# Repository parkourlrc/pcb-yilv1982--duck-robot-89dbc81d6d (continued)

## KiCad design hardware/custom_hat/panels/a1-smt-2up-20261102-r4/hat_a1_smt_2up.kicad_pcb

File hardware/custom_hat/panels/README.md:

# HAT 制造拼板工作区

2026-11-03当前86654c03，[r18](a1-smt-2up-20261102-r18/README.md)。新增BMI088 0.5mm/0.2mm F.Cu电源支路；邮票孔居中、X108/160分板带局部退铜；修复第二单元Power映射。原生主板/拼板全0，两个0.175mm探针均被Power0.2规则拒绝。旧r1～r17退出制造入口；实际工艺/制造/完整机械与首板未验。见[证据](../../../docs/references/扩展板邮票孔与电源修复/research.md)。

**旧r1～r17及其制造副本均不作当前制造依据**。第二单元Power映射不足，原DRC0不能说明规则等价；旧r14完整PCBA ZIP保留历史，不覆写。旧单板资料按源SHA审查，无B2错误。

所有文件均是制造准备/候选，不授权下单或上电。源板未解决的问题不会因为复制进拼板而消失。

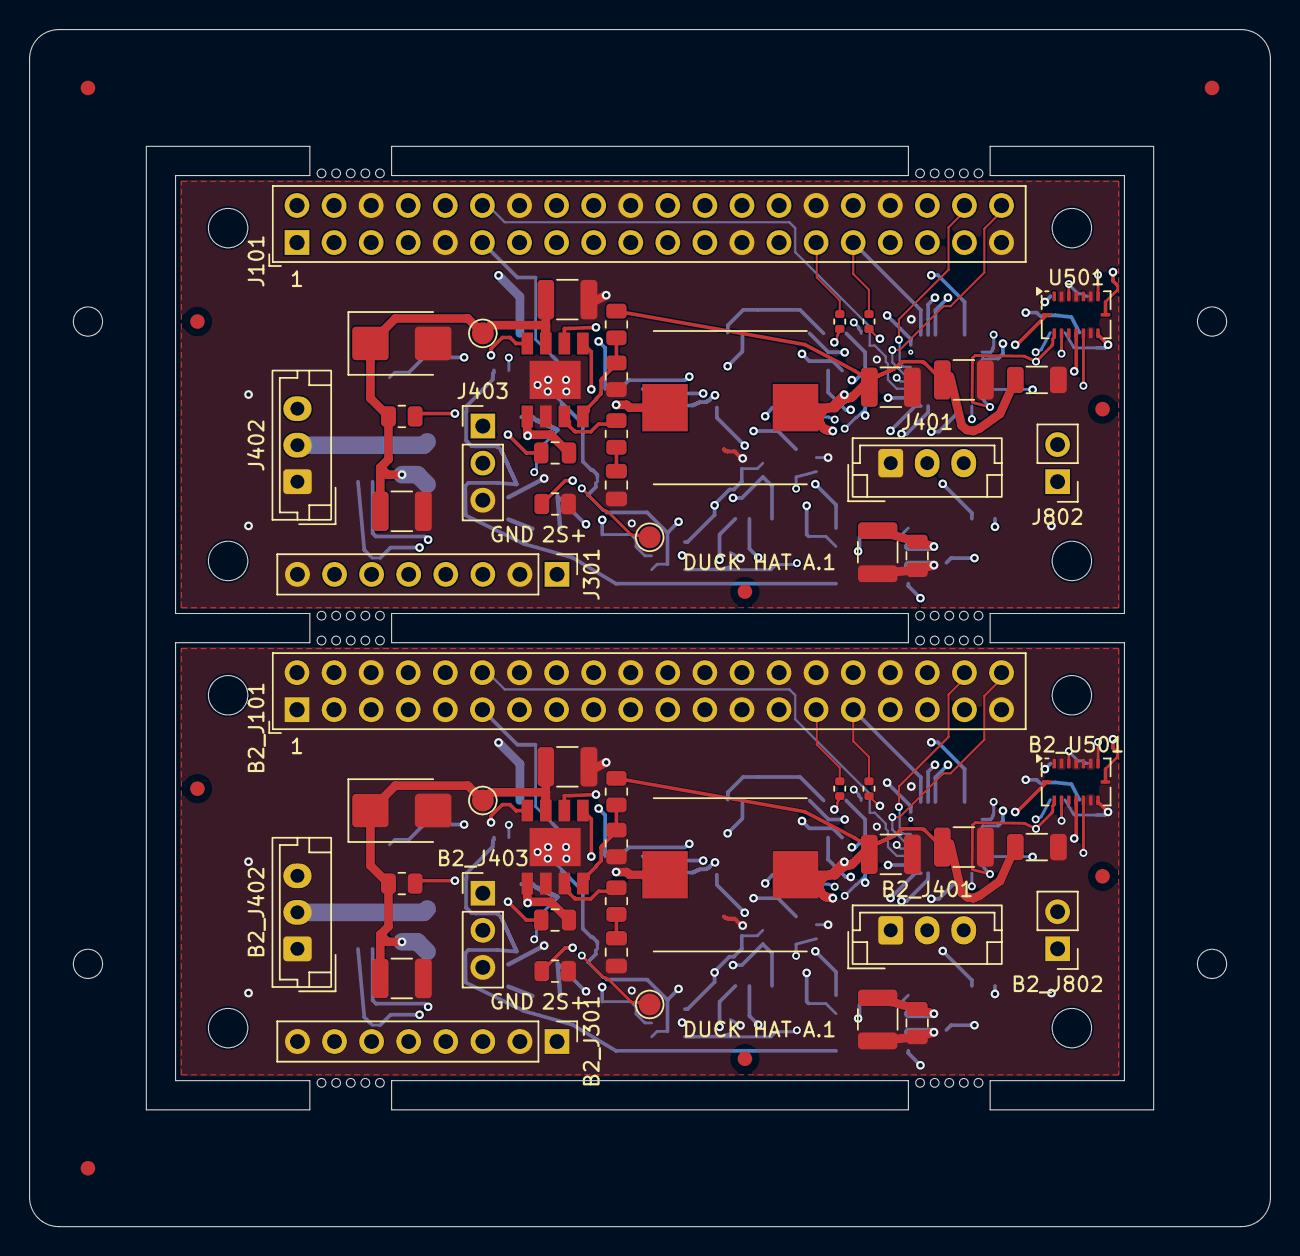
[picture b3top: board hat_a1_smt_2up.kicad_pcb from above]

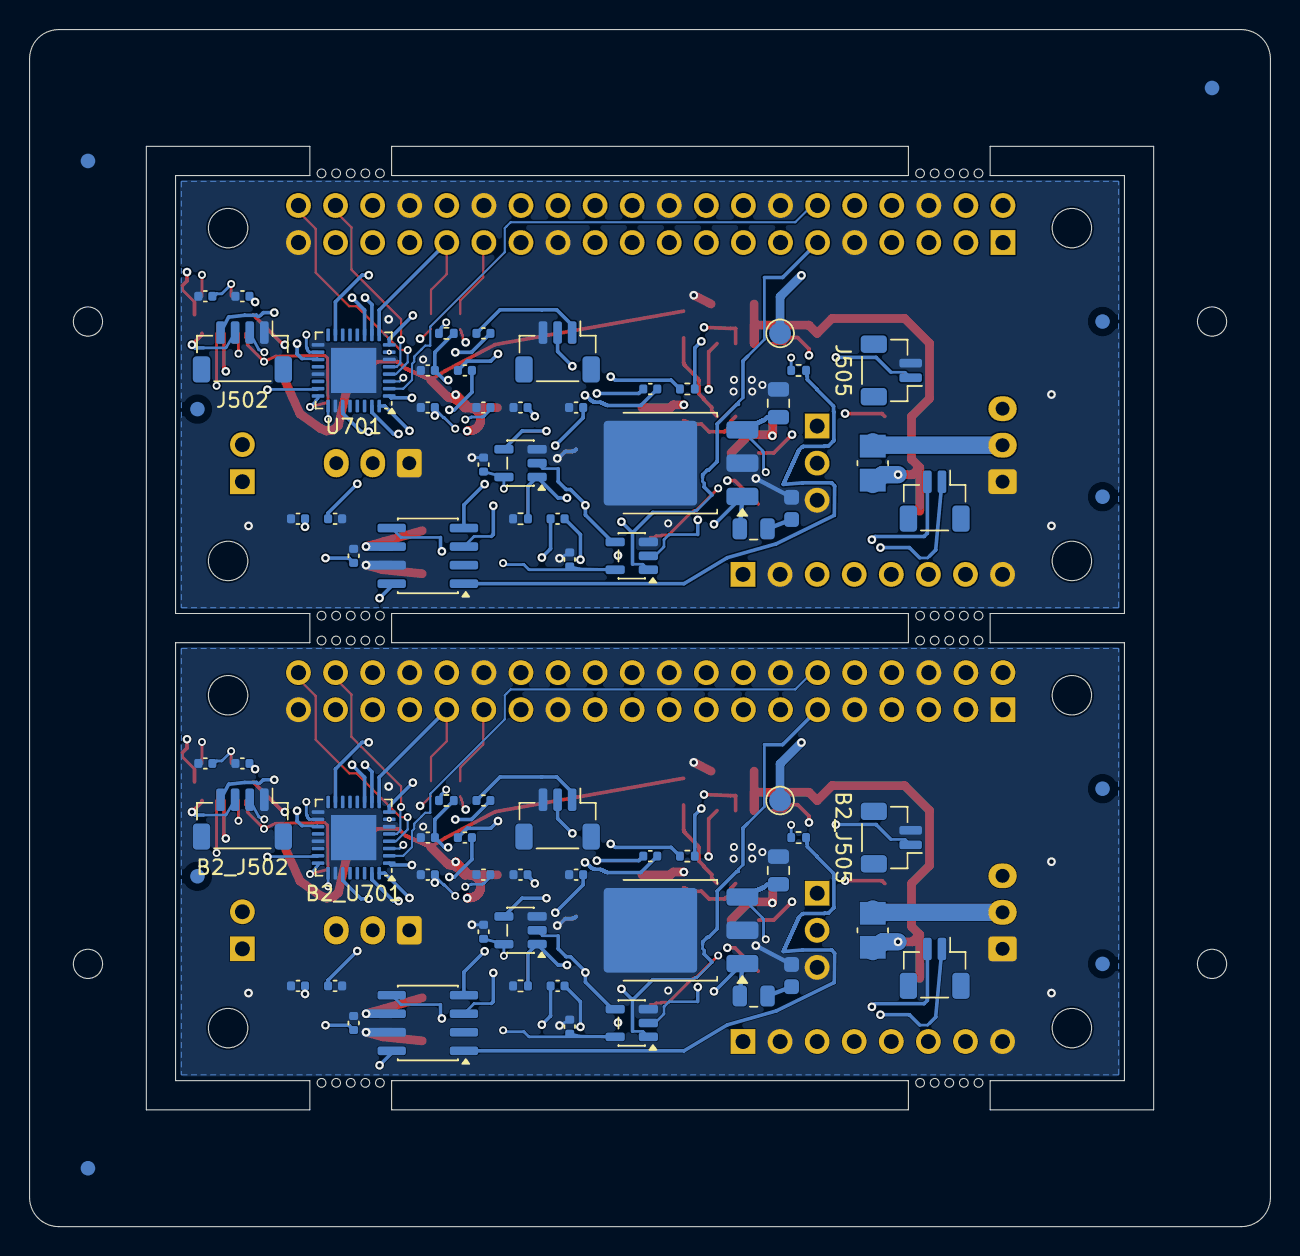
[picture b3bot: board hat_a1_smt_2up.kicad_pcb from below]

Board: 4 copper layers, 85.0 x 82.0 mm, 194 parts (77 on the bottom side), 84 nets.

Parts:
B2_C301: 3.3nF; C_0805_2012Metric
B2_C302: 100nF; C_0805_2012Metric
B2_C303, B2_C304, B2_C305, B2_C306, B2_C323: 22uF; C_1210_3225Metric
B2_C307: 22uF reserve; C_1206_3216Metric
B2_C308, B2_C328: 2.2uF; C_0805_2012Metric
B2_C309: 2.2uF; C_0805_2012Metric_LDO_ClearSilk
B2_C310, B2_C312, B2_C319, B2_C320, B2_C327, B2_C329, B2_C330: 100nF; C_0402_1005Metric
B2_C311, B2_C313, B2_C315, B2_C321, B2_C322, B2_C325, B2_C326: 1uF; C_0402_1005Metric
B2_C317, B2_C318: 10uF; C_0402_1005Metric
B2_D301: SMBJ12A (fitted); D_SMB
B2_FID1, B2_FID2, B2_FID3, B2_FID4, B2_FID5, B2_FID6: Fiducial_1mm_Mask2mm
B2_H1, B2_H2: MountingHole_2.7mm_M2.5; MountingHole_2.7_M2.5_Head4.5
B2_H3, B2_H4: MountingHole_2.7mm_M2.5
B2_J101: RADXA_ZERO_3W_40P; Radxa40P_Samtec_SSW120
B2_J301: POWER_AND_RAILS; Samtec_TSW108_07
B2_J401: DYNAMIXEL_TTL_1; JST_EH_B3B-EH-A_1x03_P2.50mm_Vertical
B2_J402: DYNAMIXEL_TTL_2; JST_EH_B3B-EH-A_1x03_P2.50mm_Vertical
B2_J403: HOST_UART2; Samtec_TSW103_07
B2_J502: TOF_I2C5; JST_SH_BM04B-SRSS-TB_1x04-1MP_P1.00mm_Vertical
B2_J504: AUDIO_OUT_SH; JST_SH_BM03B-SRSS-TB_1x03-1MP_P1.00mm_Vertical
B2_J505: MIC_IN; JST_SH_BM02B-SRSS-TB_1x02-1MP_P1.00mm_Vertical
B2_J506: SPEAKER; JST_SH_BM02B-SRSS-TB_1x02-1MP_P1.00mm_Vertical
B2_J802: IMU_INT_TP; Samtec_TSW102_07
B2_L301: 5.6uH; IHLP4040DZ_5A_Above2u2
B2_R301: 52.3k; R_0805_2012Metric
B2_R302: 10k; R_0805_2012Metric
B2_R303: 200k; R_0805_2012Metric
B2_R304: 14k; R_0805_2012Metric
B2_R305: 100k; R_0805_2012Metric
B2_R308: 10k; R_0402_1005Metric
B2_R309: 0R; Vishay_WSL1206_Jumper
B2_R310, B2_R311: 100k; R_0402_1005Metric
B2_R312: 2.2k; R_0402_1005Metric
B2_R501, B2_R502: 4.7k; R_0402_1005Metric
B2_R703: 0.047; Vishay_WSLP0603_Damping
B2_TP801: VBATT_2S_IN; TestPoint_Pad_D1.5mm
B2_TP802: +5V; TestPoint_Pad_D1.5mm
B2_TP803: +3V3; TestPoint_Pad_D1.5mm
B2_U301: AP64350; SO-8EP_AP64350
B2_U501: BMI088; Bosch_LGA-16_4.5x3mm_P0.5mm_LayoutBorder7x1y_ClockwisePinNu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
B2_U701: TLV320AIC3104; VQFN-32-1EP_5x5mm_P0.5mm_EP3.1x3.1mm
B2_U702: LP38691DT-1.8; TO-252-3_TabPin2
B2_U801: SN74LVC1G126; SOT-23-5
B2_U802: SN74LVC1G125; SOT-23-5
B2_U803: PAM8302A; SOIC-8_3.9x4.9mm_P1.27mm
C301: 3.3nF; C_0805_2012Metric
C302: 100nF; C_0805_2012Metric
C303, C304, C305, C306, C323: 22uF; C_1210_3225Metric
C307: 22uF reserve; C_1206_3216Metric
C308, C328: 2.2uF; C_0805_2012Metric
C309: 2.2uF; C_0805_2012Metric_LDO_ClearSilk
C310, C312, C319, C320, C327, C329, C330: 100nF; C_0402_1005Metric
C311, C313, C315, C321, C322, C325, C326: 1uF; C_0402_1005Metric
C317, C318: 10uF; C_0402_1005Metric
D301: SMBJ12A (fitted); D_SMB
FID1, FID2, FID3, FID4, FID5, FID6: Fiducial_1mm_Mask2mm
H1, H2: MountingHole_2.7mm_M2.5; MountingHole_2.7_M2.5_Head4.5
H3, H4: MountingHole_2.7mm_M2.5
J101: RADXA_ZERO_3W_40P; Radxa40P_Samtec_SSW120
J301: POWER_AND_RAILS; Samtec_TSW108_07
J401: DYNAMIXEL_TTL_1; JST_EH_B3B-EH-A_1x03_P2.50mm_Vertical
J402: DYNAMIXEL_TTL_2; JST_EH_B3B-EH-A_1x03_P2.50mm_Vertical
J403: HOST_UART2; Samtec_TSW103_07
J502: TOF_I2C5; JST_SH_BM04B-SRSS-TB_1x04-1MP_P1.00mm_Vertical
J504: AUDIO_OUT_SH; JST_SH_BM03B-SRSS-TB_1x03-1MP_P1.00mm_Vertical
J505: MIC_IN; JST_SH_BM02B-SRSS-TB_1x02-1MP_P1.00mm_Vertical
J506: SPEAKER; JST_SH_BM02B-SRSS-TB_1x02-1MP_P1.00mm_Vertical
J802: IMU_INT_TP; Samtec_TSW102_07
L301: 5.6uH; IHLP4040DZ_5A_Above2u2
MB1, MB2, MB3, MB4, MB5, MB6, MB7, MB8, MB9, MB10, MB11, MB12, MB13, MB14, MB15, MB16, MB17, MB18, MB19, MB20, MB21, MB22, MB23, MB24, MB25, MB26, MB27, MB28, MB29, MB30, MB31, MB32, MB33, MB34, MB35, MB36, MB37, MB38, MB39, MB40: Panel NPTH
PFID_B1, PFID_B2, PFID_B3: Panel fiducial 1mm/2mm
PFID_F1, PFID_F2, PFID_F3: Panel fiducial 1mm/2mm
PH1, PH2, PH3, PH4: Panel NPTH
R301: 52.3k; R_0805_2012Metric
R302: 10k; R_0805_2012Metric
R303: 200k; R_0805_2012Metric
R304: 14k; R_0805_2012Metric
R305: 100k; R_0805_2012Metric
R308: 10k; R_0402_1005Metric
R309: 0R; Vishay_WSL1206_Jumper
R310, R311: 100k; R_0402_1005Metric
R312: 2.2k; R_0402_1005Metric
R501, R502: 4.7k; R_0402_1005Metric
R703: 0.047; Vishay_WSLP0603_Damping
TP801: VBATT_2S_IN; TestPoint_Pad_D1.5mm
TP802: +5V; TestPoint_Pad_D1.5mm
TP803: +3V3; TestPoint_Pad_D1.5mm
U301: AP64350; SO-8EP_AP64350
U501: BMI088; Bosch_LGA-16_4.5x3mm_P0.5mm_LayoutBorder7x1y_ClockwisePinNu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
U701: TLV320AIC3104; VQFN-32-1EP_5x5mm_P0.5mm_EP3.1x3.1mm
U702: LP38691DT-1.8; TO-252-3_TabPin2
U801: SN74LVC1G126; SOT-23-5
U802: SN74LVC1G125; SOT-23-5
U803: PAM8302A; SOIC-8_3.9x4.9mm_P1.27mm

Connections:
+1V8_CODEC: C309.1, C311.1, J301.6, U701.32, U702.1
+3V3: C308.1, C312.1, C313.1, C315.1, C319.1, C320.1, C329.1, C330.1, J101.1, J101.17, J301.4, J502.2, R308.2, R311.2, R501.1, R502.1, TP803.1, U501.3, U501.7, U501.11, U501.14, U501.15, U701.7, U701.18, U701.24, U701.25, U702.3, U801.5, U802.5
+5V: C305.1, C306.1, C307.1, C323.1, C328.1, J101.2, J101.4, J301.3, L301.2, R301.1, TP802.1, U803.6
+5V_FB: R301.2, R302.1, U301.5
AUDIO_AMP_EN: R311.1, U803.1
AUDIO_AMP_INN: C322.1, U803.4
AUDIO_AMP_INP: C321.2, U803.3
AUDIO_HP_L: C317.1, U701.19
AUDIO_HP_R: C318.1, U701.23
AUDIO_L: C317.2, J504.1
AUDIO_LINE_L: C321.1, U701.27
AUDIO_MIC: C325.1, J505.1, R312.2
AUDIO_MIC_AC: C325.2, U701.10
AUDIO_MIC_BIAS: C327.1, R312.1, U701.15
AUDIO_MIC_REF: C326.2, U701.11
AUDIO_R: C318.2, J504.2
B2/+1V8_CODEC: B2_C309.1, B2_C311.1, B2_J301.6, B2_U701.32, B2_U702.1
B2/+3V3: B2_C308.1, B2_C312.1, B2_C313.1, B2_C315.1, B2_C319.1, B2_C320.1, B2_C329.1, B2_C330.1, B2_J101.1, B2_J101.17, B2_J301.4, B2_J502.2, B2_R308.2, B2_R311.2, B2_R501.1, B2_R502.1, B2_TP803.1, B2_U501.3, B2_U501.7, B2_U501.11, B2_U501.14, B2_U501.15, B2_U701.7, B2_U701.18, B2_U701.24, B2_U701.25, B2_U702.3, B2_U801.5, B2_U802.5
B2/+5V: B2_C305.1, B2_C306.1, B2_C307.1, B2_C323.1, B2_C328.1, B2_J101.2, B2_J101.4, B2_J301.3, B2_L301.2, B2_R301.1, B2_TP802.1, B2_U803.6
B2/+5V_FB: B2_R301.2, B2_R302.1, B2_U301.5
B2/AUDIO_AMP_EN: B2_R311.1, B2_U803.1
B2/AUDIO_AMP_INN: B2_C322.1, B2_U803.4
B2/AUDIO_AMP_INP: B2_C321.2, B2_U803.3
B2/AUDIO_HP_L: B2_C317.1, B2_U701.19
B2/AUDIO_HP_R: B2_C318.1, B2_U701.23
B2/AUDIO_L: B2_C317.2, B2_J504.1
B2/AUDIO_LINE_L: B2_C321.1, B2_U701.27
B2/AUDIO_MIC: B2_C325.1, B2_J505.1, B2_R312.2
B2/AUDIO_MIC_AC: B2_C325.2, B2_U701.10
B2/AUDIO_MIC_BIAS: B2_C327.1, B2_R312.1, B2_U701.15
B2/AUDIO_MIC_REF: B2_C326.2, B2_U701.11
B2/AUDIO_R: B2_C318.2, B2_J504.2
B2/BMI_INT1_TP: B2_J802.1, B2_U501.16
B2/BMI_INT3_TP: B2_J802.2, B2_U501.12
B2/BUCK_BST: B2_C302.1, B2_U301.1
B2/BUCK_COMP: B2_R304.1, B2_U301.6
B2/BUCK_EN: B2_R305.2, B2_U301.3
B2/BUCK_RT: B2_R303.1, B2_U301.4
B2/BUCK_SW: B2_C302.2, B2_L301.1, B2_U301.8
B2/CODEC_RST: B2_C310.1, B2_J101.33, B2_R308.1, B2_U701.31
B2/COMP_RC: B2_C301.1, B2_R304.2
B2/DXL_DATA: B2_J401.3, B2_J402.3, B2_U801.4, B2_U802.2
B2/DXL_DIR: B2_J101.11, B2_R310.1, B2_U801.1, B2_U802.1
B2/I2C5_SCL: B2_J101.29, B2_J502.4, B2_R501.2, B2_U501.8, B2_U701.8
B2/I2C5_SDA: B2_J101.31, B2_J502.3, B2_R502.2, B2_U501.9, B2_U701.9
B2/I2S_BCLK: B2_J101.12, B2_U701.2
B2/I2S_LRCK: B2_J101.35, B2_U701.3
B2/I2S_MCLK: B2_J101.13, B2_U701.1
B2/I2S_SDI: B2_J101.38, B2_U701.5
B2/I2S_SDO: B2_J101.40, B2_U701.4
B2/LDO_CAP_RETURN: B2_C309.2, B2_R703.1
B2/POWER_GND: B2_C301.2, B2_C303.2, B2_C304.2, B2_C305.2, B2_C306.2, B2_C307.2, B2_C308.2, B2_C310.2, B2_C311.2, B2_C312.2, B2_C313.2, B2_C315.2, B2_C319.2, B2_C320.2, B2_C322.2, B2_C323.2, B2_C326.1, B2_C327.2, B2_C328.2, B2_C329.2, B2_C330.2, B2_D301.2, B2_J101.6, B2_J101.9, B2_J101.14, B2_J101.20, B2_J101.25, B2_J101.30, B2_J101.34, B2_J101.39, B2_J301.2, B2_J301.8, B2_J401.1, B2_J402.1, B2_J403.3, B2_J502.1, B2_J504.3, B2_J505.2, B2_R302.2, B2_R303.2, B2_R310.2, B2_R703.2, B2_U301.7, B2_U301.9, B2_U501.2, B2_U501.4, B2_U501.6, B2_U501.10, B2_U701.6, B2_U701.17, B2_U701.21, B2_U701.26, B2_U701.33, B2_U702.2, B2_U801.3, B2_U802.3, B2_U803.7
B2/SERVO_VBAT: B2_J301.7, B2_J401.2, B2_J402.2, B2_R309.2
B2/SPK_N: B2_J506.2, B2_U803.8
B2/SPK_P: B2_J506.1, B2_U803.5
B2/UART2_RX: B2_J101.10, B2_J403.2, B2_U802.4
B2/UART2_TX: B2_J101.8, B2_J403.1, B2_U801.2
B2/VBATT_2S_IN: B2_C303.1, B2_C304.1, B2_D301.1, B2_J301.1, B2_R305.1, B2_R309.1, B2_TP801.1, B2_U301.2
BMI_INT1_TP: J802.1, U501.16
BMI_INT3_TP: J802.2, U501.12
BUCK_BST: C302.1, U301.1
BUCK_COMP: R304.1, U301.6
BUCK_EN: R305.2, U301.3
BUCK_RT: R303.1, U301.4
BUCK_SW: C302.2, L301.1, U301.8
CODEC_RST: C310.1, J101.33, R308.1, U701.31
COMP_RC: C301.1, R304.2
DXL_DATA: J401.3, J402.3, U801.4, U802.2
DXL_DIR: J101.11, R310.1, U801.1, U802.1
I2C5_SCL: J101.29, J502.4, R501.2, U501.8, U701.8
I2C5_SDA: J101.31, J502.3, R502.2, U501.9, U701.9
I2S_BCLK: J101.12, U701.2
I2S_LRCK: J101.35, U701.3
I2S_MCLK: J101.13, U701.1
I2S_SDI: J101.38, U701.5
I2S_SDO: J101.40, U701.4
LDO_CAP_RETURN: C309.2, R703.1
POWER_GND: C301.2, C303.2, C304.2, C305.2, C306.2, C307.2, C308.2, C310.2, C311.2, C312.2, C313.2, C315.2, C319.2, C320.2, C322.2, C323.2, C326.1, C327.2, C328.2, C329.2, C330.2, D301.2, J101.6, J101.9, J101.14, J101.20, J101.25, J101.30, J101.34, J101.39, J301.2, J301.8, J401.1, J402.1, J403.3, J502.1, J504.3, J505.2, R302.2, R303.2, R310.2, R703.2, U301.7, U301.9, U501.2, U501.4, U501.6, U501.10, U701.6, U701.17, U701.21, U701.26, U701.33, U702.2, U801.3, U802.3, U803.7
SERVO_VBAT: J301.7, J401.2, J402.2, R309.2
SPK_N: J506.2, U803.8
SPK_P: J506.1, U803.5
UART2_RX: J101.10, J403.2, U802.4
UART2_TX: J101.8, J403.1, U801.2
VBATT_2S_IN: C303.1, C304.1, D301.1, J301.1, R305.1, R309.1, TP801.1, U301.2

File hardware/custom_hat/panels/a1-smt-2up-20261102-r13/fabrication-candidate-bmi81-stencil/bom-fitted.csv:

Reference,Qty,Value,Footprint,MPN,Manufacturer,DNP
"C301,B2_C301",2,3.3nF,Capacitor_SMD:C_0805_2012Metric,08055A332JAT2A,KYOCERA AVX,False
"C302,B2_C302",2,100nF,Capacitor_SMD:C_0805_2012Metric,C0805C104K5RACTU,KEMET,False
"C303,C304,C305,C306,C323,B2_C303,B2_C304,B2_C305,B2_C306,B2_C323",10,22uF,Capacitor_SMD:C_1210_3225Metric,C1210C226K3RACTU,KEMET,False
"C308,C328,B2_C308,B2_C328",4,2.2uF,Capacitor_SMD:C_0805_2012Metric,C0805C225K5RACTU,KEMET,False
"C309,B2_C309",2,2.2uF,duck:C_0805_2012Metric_LDO_ClearSilk,C0805C225K5RACTU,KEMET,False
"C310,C312,C319,C320,C327,C329,C330,B2_C310,B2_C312,B2_C319,B2_C320,B2_C327,B2_C329,B2_C330",14,100nF,Capacitor_SMD:C_0402_1005Metric,C0402C104K3RACTU,KEMET,False
"C311,C313,C315,C321,C322,C325,C326,B2_C311,B2_C313,B2_C315,B2_C321,B2_C322,B2_C325,B2_C326",14,1uF,Capacitor_SMD:C_0402_1005Metric,C0402C105K4PACTU,KEMET,False
"C317,C318,B2_C317,B2_C318",4,10uF,Capacitor_SMD:C_0402_1005Metric,C0402C106M9PACTU,KEMET,False
"D301,B2_D301",2,SMBJ12A (fitted),Diode_SMD:D_SMB,SMBJ12A-E3/52,Vishay,False
"J101,B2_J101",2,RADXA_ZERO_3W_40P,duck:Radxa40P_Samtec_SSW120,SSW-120-01-G-D,Samtec,False
"J301,B2_J301",2,POWER_AND_RAILS,duck:Samtec_TSW108_07,TSW-108-07-G-S,Samtec,False
"J401,B2_J401",2,DYNAMIXEL_TTL_1,Connector_JST:JST_EH_B3B-EH-A_1x03_P2.50mm_Vertical,B3B-EH-A(LF)(SN),JST,False
"J402,B2_J402",2,DYNAMIXEL_TTL_2,Connector_JST:JST_EH_B3B-EH-A_1x03_P2.50mm_Vertical,B3B-EH-A(LF)(SN),JST,False
"J403,B2_J403",2,HOST_UART2,duck:Samtec_TSW103_07,TSW-103-07-G-S,Samtec,False
"J502,B2_J502",2,TOF_I2C5,Connector_JST:JST_SH_BM04B-SRSS-TB_1x04-1MP_P1.00mm_Vertical,BM04B-SRSS-TB(LF)(SN),JST,False
"J504,B2_J504",2,AUDIO_OUT_SH,Connector_JST:JST_SH_BM03B-SRSS-TB_1x03-1MP_P1.00mm_Vertical,BM03B-SRSS-TB(LF)(SN),JST,False
"J505,B2_J505",2,MIC_IN,Connector_JST:JST_SH_BM02B-SRSS-TB_1x02-1MP_P1.00mm_Vertical,BM02B-SRSS-TB(LF)(SN),JST,False
"J506,B2_J506",2,SPEAKER,Connector_JST:JST_SH_BM02B-SRSS-TB_1x02-1MP_P1.00mm_Vertical,BM02B-SRSS-TB(LF)(SN),JST,False
"J802,B2_J802",2,IMU_INT_TP,duck:Samtec_TSW102_07,TSW-102-07-G-S,Samtec,False
"L301,B2_L301",2,5.6uH,duck:IHLP4040DZ_5A_Above2u2,IHLP4040DZER5R6M5A,Vishay,False
"R301,B2_R301",2,52.3k,Resistor_SMD:R_0805_2012Metric,CRCW080552K3FKEA,Vishay,False
"R302,B2_R302",2,10k,Resistor_SMD:R_0805_2012Metric,CRCW080510K0FKEA,Vishay,False
"R303,B2_R303",2,200k,Resistor_SMD:R_0805_2012Metric,CRCW0805200KFKEA,Vishay,False
"R304,B2_R304",2,14k,Resistor_SMD:R_0805_2012Metric,CRCW080514K0FKEA,Vishay,False
"R305,B2_R305",2,100k,Resistor_SMD:R_0805_2012Metric,CRCW0805100KFKEA,Vishay,False
"R308,B2_R308",2,10k,Resistor_SMD:R_0402_1005Metric,CRCW040210K0FKED,Vishay,False
"R309,B2_R309",2,0R,duck:Vishay_WSL1206_Jumper,WSL120600000ZEA9,Vishay,False
"R310,R311,B2_R310,B2_R311",4,100k,Resistor_SMD:R_0402_1005Metric,CRCW0402100KFKED,Vishay,False
"R312,B2_R312",2,2.2k,Resistor_SMD:R_0402_1005Metric,CRCW04022K20FKED,Vishay,False
"R501,R502,B2_R501,B2_R502",4,4.7k,Resistor_SMD:R_0402_1005Metric,CRCW04024K70FKED,Vishay,False
"R703,B2_R703",2,0.047,duck:Vishay_WSLP0603_Damping,WSLP0603R0470FEA,Vishay,False
"U301,B2_U301",2,AP64350,duck:SO-8EP_AP64350,AP64350SP-13,Diodes Incorporated,False
"U501,B2_U501",2,BMI088,Package_LGA:Bosch_LGA-16_4.5x3mm_P0.5mm_LayoutBorder7x1y_ClockwisePinNumbering,BMI088,Bosch Sensortec,False
"U701,B2_U701",2,TLV320AIC3104,duck:TI_RHB0032E_AIC3104_EP345,TLV320AIC3104IRHBR,Texas Instruments,False
"U702,B2_U702",2,LP38691DT-1.8,duck:TI_NDP0003B_LP38691_PasteGrid,LP38691DT-1.8/NOPB,Texas Instruments,False
"U801,B2_U801",2,SN74LVC1G126,Package_TO_SOT_SMD:SOT-23-5,SN74LVC1G126DBVR,Texas Instruments,False
"U802,B2_U802",2,SN74LVC1G125,Package_TO_SOT_SMD:SOT-23-5,SN74LVC1G125DBVT,Texas Instruments,False
"U803,B2_U803",2,PAM8302A,Package_SO:SOIC-8_3.9x4.9mm_P1.27mm,PAM8302AADCR,Diodes Incorporated,False
